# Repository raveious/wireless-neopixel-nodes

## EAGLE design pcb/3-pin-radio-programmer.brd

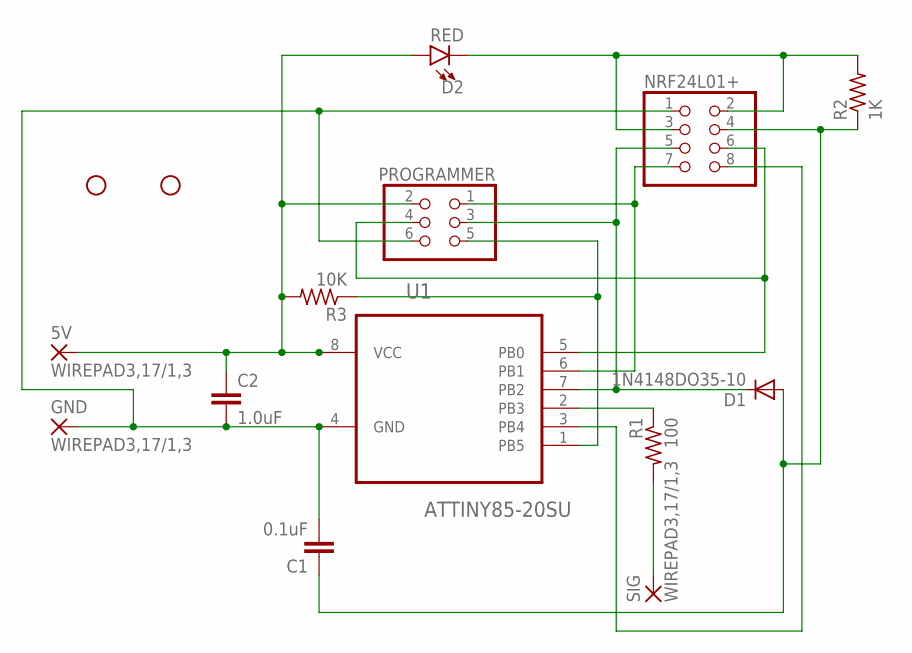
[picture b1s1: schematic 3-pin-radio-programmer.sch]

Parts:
5V: WIREPAD3,17/1,3; 3,17/1,3
C1: 0.1uF; 0603
C2: 1.0uF; 0603
D1: 1N4148DO35-10; DO35-10
D2: RED; LED_3MM
GND: WIREPAD3,17/1,3; 3,17/1,3
H1, H2: STAND-OFF
NRF24L01+: PINHD-2X4; 2X04
PROGRAMMER: PINHD-2X3; 2X03
R1: 100; R0805
R2: 1K; R0805
R3: 10K; R0805
SIG: WIREPAD3,17/1,3; 3,17/1,3
U1: ATTINY85-20SU; SOIC127P798X216-8N

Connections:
unnamed: NRF24L01+.6, PROGRAMMER.4, U1.5 (PB0)
unnamed: C1.2, C2.2, GND.1, NRF24L01+.1, PROGRAMMER.6, U1.4 (GND)
unnamed: R1.1, U1.2 (PB3)
unnamed: R1.2, SIG.1
unnamed: D1.C, NRF24L01+.5, PROGRAMMER.3, U1.7 (PB2)
unnamed: C1.1, D1.A, NRF24L01+.4, R2.1
unnamed: D2.K (C), NRF24L01+.2, NRF24L01+.3, R2.2
unnamed: NRF24L01+.8, U1.3 (PB4)
unnamed: NRF24L01+.7, PROGRAMMER.1, U1.6 (PB1)
unnamed: 5V.1, C2.1, D2.A, PROGRAMMER.2, R3.2, U1.8 (VCC)
unnamed: PROGRAMMER.5, R3.1, U1.1 (PB5)

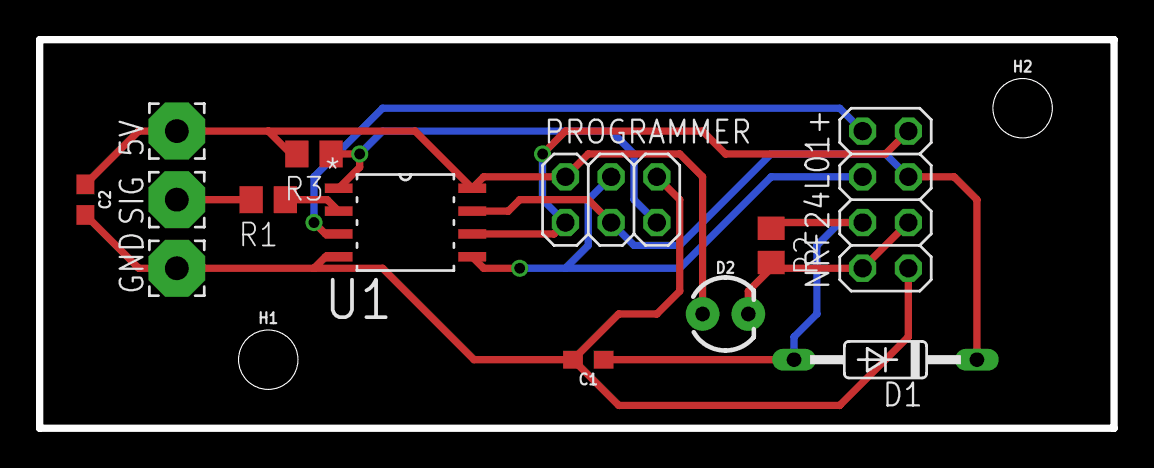
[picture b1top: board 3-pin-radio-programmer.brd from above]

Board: 2 copper layers, 59.7 x 21.6 mm, 15 parts (0 on the bottom side), 11 nets.

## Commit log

2017-01-24 Initial board design
    Adding in initial board design. Board was just ordered from OSH Park
    today, lets hope for the best.
2017-02-16 Adding pull up on reset pin

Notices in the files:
parts and their libraries:
SparkFun-Capacitors: Licensing: Creative Commons ShareAlike 4.0 International - https://creativecommons.org/licenses/by-sa/4.0
